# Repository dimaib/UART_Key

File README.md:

# Smart lock for city scooters
## Description
- This device allows you to block the scooter when charging, preventing premature removal from the rack
- The device also determines whether the scooter is rented or not, thereby blocking or giving it away
- Allows you to determine the speed of the scooter and dynamically change the color of the LED strip depending on the speed.
	>All data is intercepted from UART data line of the scooter.
## Tools and languages
- PCB and circuit diagram created by Altium Designer
- Firmware created in Keil uVision for ARM in C languages

## Main view PCB

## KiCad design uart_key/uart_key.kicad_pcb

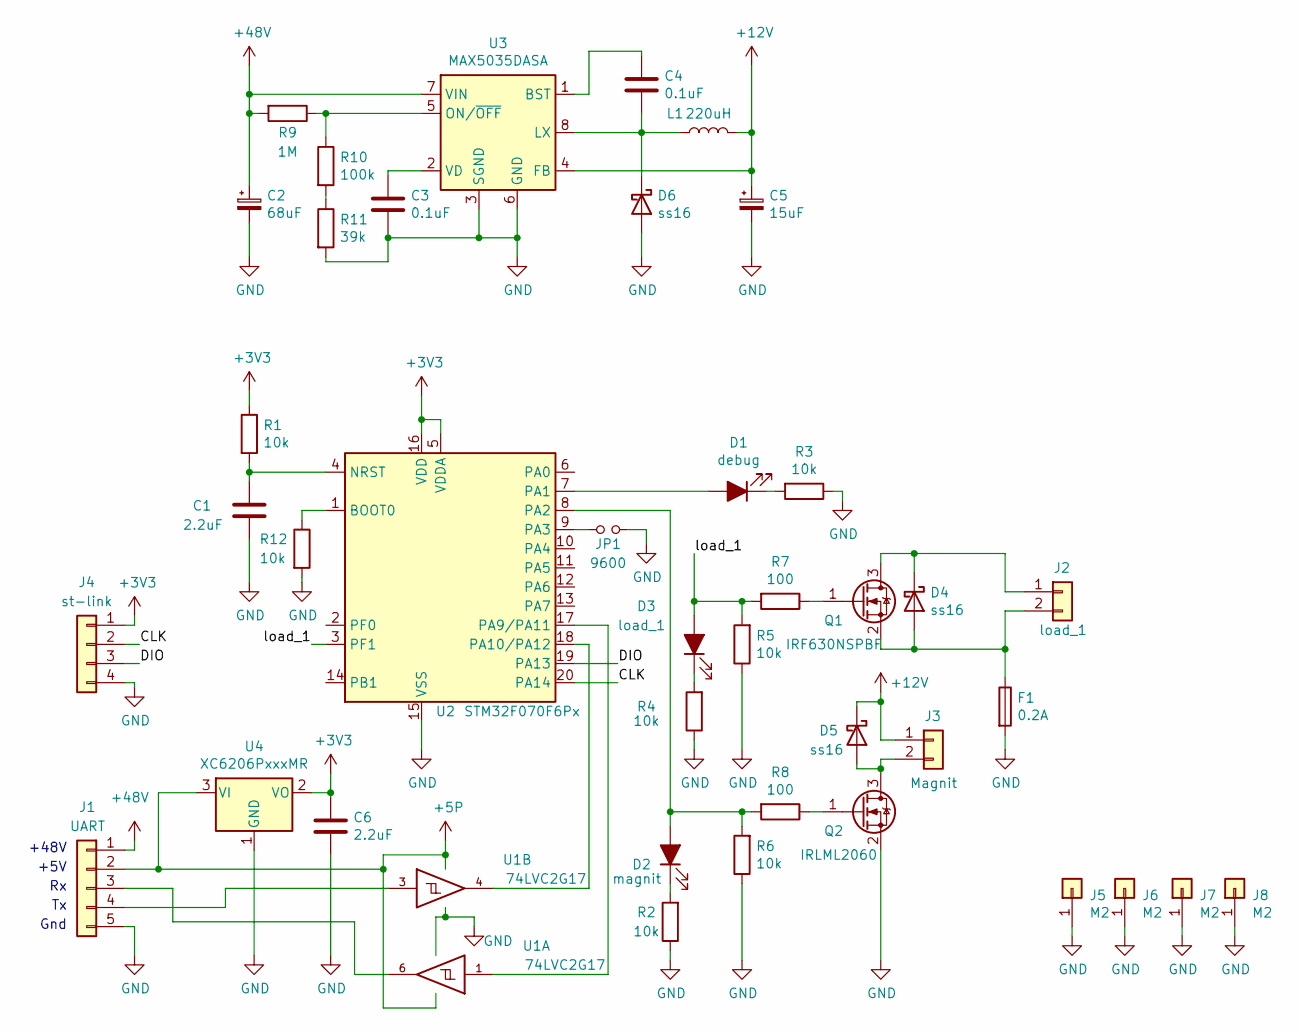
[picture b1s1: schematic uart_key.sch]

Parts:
C1, C6: 2.2uF; C_0603_1608Metric
C2: 68uF; CP_Elec_10x10.5
C3, C4: 0.1uF; C_0603_1608Metric
C5: 15uF; CP_EIA-3528-21_Kemet-B
D1: debug; LED_0603_1608Metric_Castellated
D2: magnit; LED_0603_1608Metric_Castellated
D3: load_1; LED_0603_1608Metric_Castellated
D4, D5, D6: ss16; D_SMA
F1: 0.2А; Fuse_1812_4532Metric
J1: UART; JST_XH_B5B-XH-A_1x05_P2.50mm_Vertical
J2: load_1; magnet_conn
J3: Magnit; ZH_Conn_02x01
J4: st-link; ZH_Conn_04x01
J5, J6, J7, J8: M2; MountingHole_2.2mm_M2_ISO7380_Pad_TopBottom
JP1: 9600; SolderJumper-2_P1.3mm_Open_TrianglePad1.0x1.5mm
L1: 220uH; L_10.4x10.4_H4.8
Q1: IRF630NSPBF; TO-263-2
Q2: IRLML2060; SOT-23
R1, R2, R3, R4, R5, R6, R12: 10k; R_0603_1608Metric
R7, R8: 100; R_0603_1608Metric
R9: 1M; R_0603_1608Metric
R10: 100k; R_0603_1608Metric
R11: 39k; R_0603_1608Metric
U1: 74LVC2G17; SOT-23-6
U2: STM32F070F6Px; TSSOP-20_4.4x6.5mm_P0.65mm
U3: MAX5035DASA; SOIC-8_3.9x4.9mm_P1.27mm
U4: XC6206PxxxMR; SOT-23

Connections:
+3V3: C6.1, J4.1, R1.1, U2.5 (VDDA), U2.16 (VDD), U4.2 (VO)
+5P: J1.2, U1.5 (VCC), U4.3 (VI)
+12V: C5.1, D5.1 (K), J3.1, L1.2, U3.4 (FB)
+48V: C2.1, J1.1, R9.2, U3.7 (VIN)
/CLK: J4.2, U2.20 (PA14)
/DIO: J4.3, U2.19 (PA13)
/load_1: D3.2 (A), R5.2, R7.2, U2.3 (PF1)
GND: C1.2, C2.2, C3.2, C5.2, C6.2, D6.2 (A), F1.2, J1.5, J4.4, J5.1, J6.1, J7.1, J8.1, JP1.2, Q2.2 (S), R2.1, R3.1, R4.1, R5.1, R6.1, R11.2, R12.2, U1.2 (GND), U2.15 (VSS), U3.3 (SGND), U3.6 (GND), U4.1 (GND)
unnamed: C1.1, R1.2, U2.4 (NRST)
unnamed: C3.1, U3.2 (VD)
unnamed: C4.1, U3.1 (BST)
unnamed: C4.2, D6.1 (K), L1.1, U3.8 (LX)
unnamed: D1.1 (K), R3.2
unnamed: D1.2 (A), U2.7 (PA1)
unnamed: D2.1 (K), R2.2
unnamed: D2.2 (A), R6.2, R8.2, U2.8 (PA2)
unnamed: D3.1 (K), R4.2
unnamed: D4.1 (K), J2.1, Q1.3 (D)
unnamed: D4.2 (A), F1.1, J2.2, Q1.2 (S)
unnamed: D5.2 (A), J3.2, Q2.3 (D)
unnamed: J1.3, U1.6
unnamed: J1.4, U1.3
unnamed: JP1.1, U2.9 (PA3)
unnamed: Q1.1 (G), R7.1
unnamed: Q2.1 (G), R8.1
unnamed: R9.1, R10.1, U3.5 (ON/~OFF~)
unnamed: R10.2, R11.1
unnamed: R12.1, U2.1 (BOOT0)
unnamed: U1.1, U2.17 (PA9/PA11)
unnamed: U1.4, U2.18 (PA10/PA12)

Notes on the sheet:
+5V
Gnd
+48V

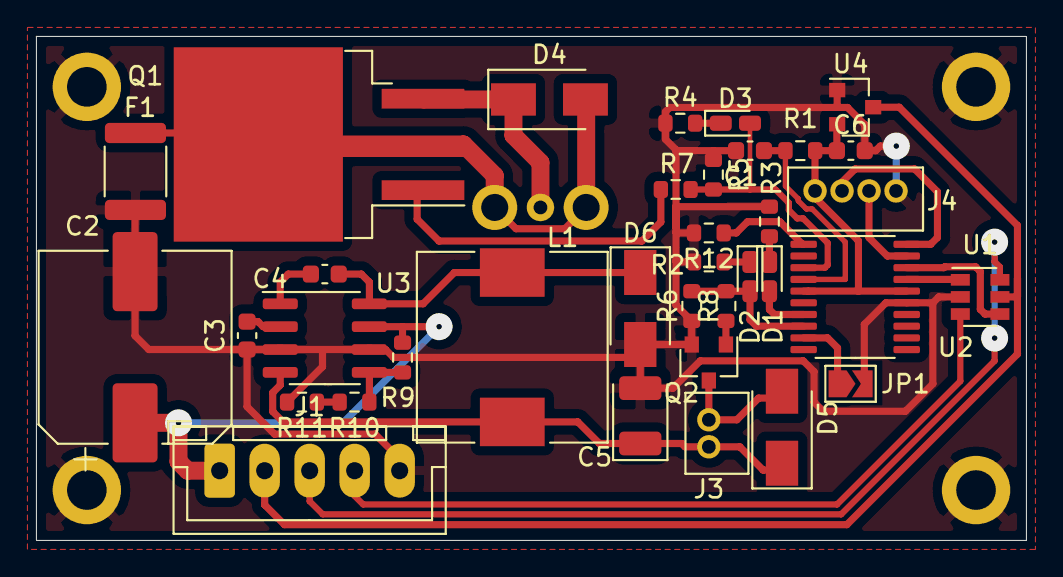
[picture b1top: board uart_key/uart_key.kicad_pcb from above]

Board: 2 copper layers, 55.0 x 28.0 mm, 41 parts (0 on the bottom side), 30 nets.

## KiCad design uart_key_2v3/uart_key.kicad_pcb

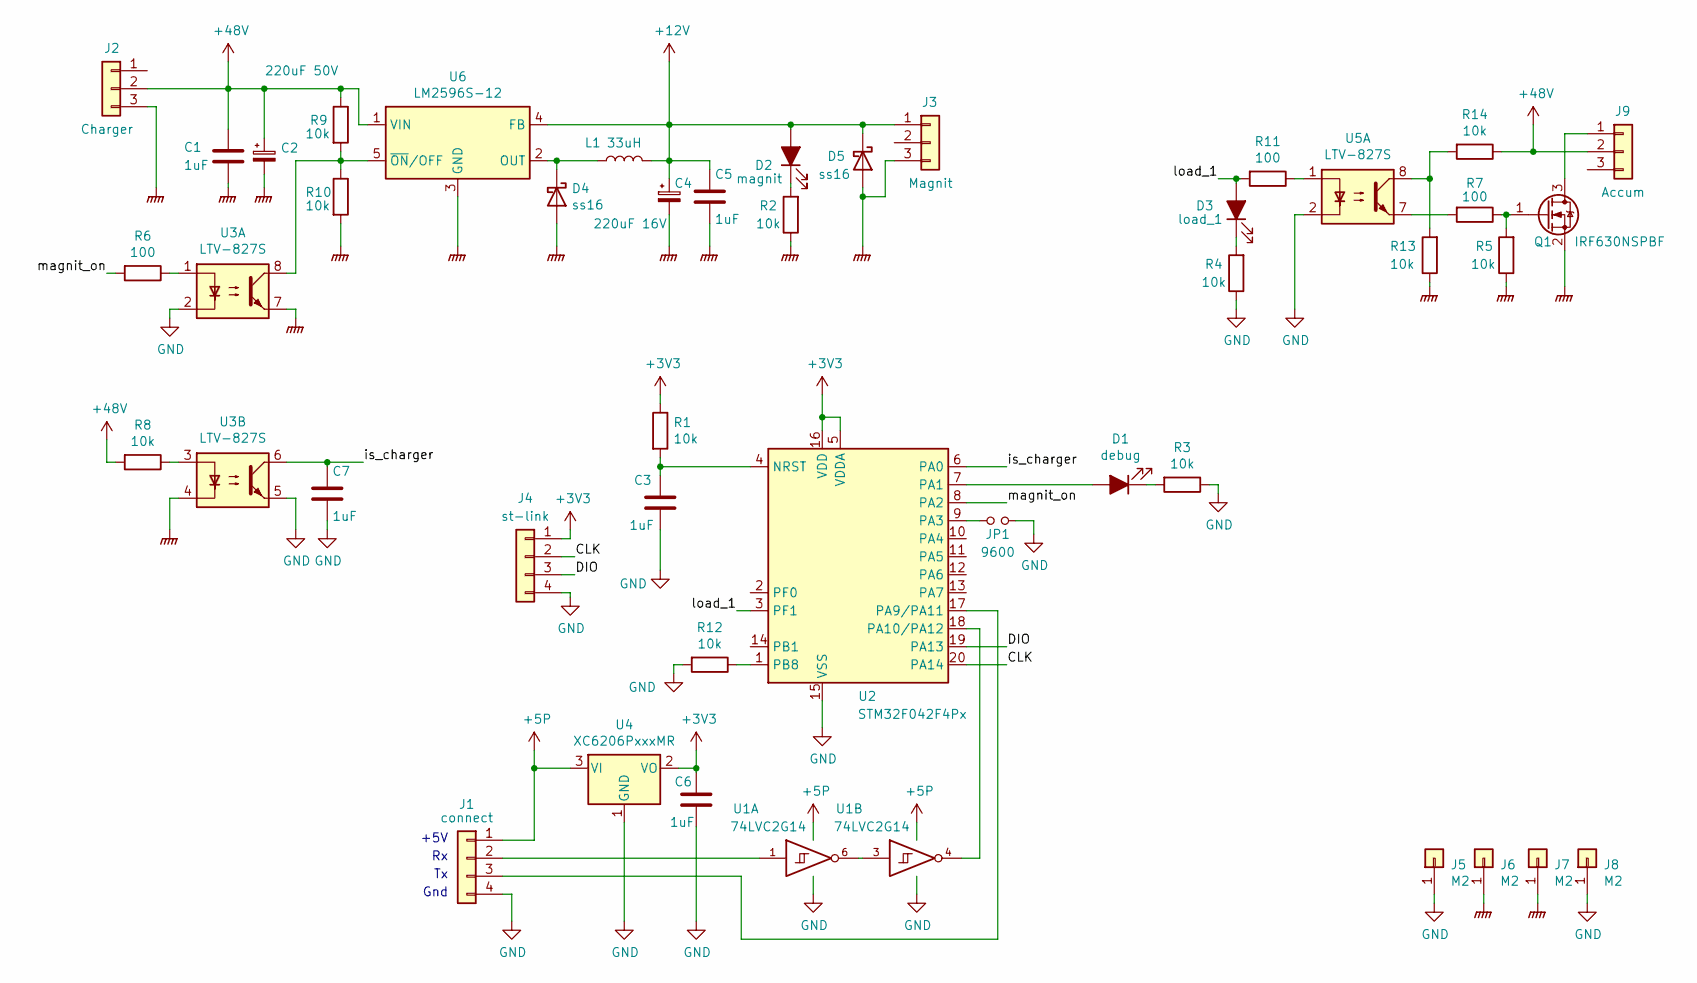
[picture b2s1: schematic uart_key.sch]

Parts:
C1, C3, C5, C6, C7: 1uF; C_0603_1608Metric
C2: 220uF 50V; CP_Elec_10x10.5
C4: 220uF 16V; CP_Elec_6.3x7.7
D1: debug; LED_0603_1608Metric_Castellated
D2: magnit; LED_0603_1608Metric_Castellated
D3: load_1; LED_0603_1608Metric_Castellated
D4, D5: ss16; D_SMA
J1: connect; JST_XH_B4B-XH-A_1x04_P2.50mm_Vertical
J2: Charger; JST_XH_B3B-XH-A_1x03_P2.50mm_Vertical
J3: Magnit; JST_XH_B3B-XH-A_1x03_P2.50mm_Vertical
J4: st-link; ZH_Conn_04x01
J5, J6, J7, J8: M2; MountingHole_2.2mm_M2_Pad_Via
J9: Accum; JST_XH_B3B-XH-A_1x03_P2.50mm_Vertical
JP1: 9600; PinHeader_1x02_P2.54mm_Vertical
L1: 33uH; SDR_1006
Q1: IRF630NSPBF; TO-263-2
R1, R2, R3, R4, R5, R8, R9, R10, R12, R13, R14: 10k; R_0603_1608Metric
R6, R7, R11: 100; R_0603_1608Metric
U1: 74LVC2G14; SOT-23-6
U2: STM32F042F4Px; TSSOP-20_4.4x6.5mm_P0.65mm
U3, U5: LTV-827S; SMDIP-8_W9.53mm
U4: XC6206PxxxMR; SOT-23
U6: LM2596S-12; TO-263-5_TabPin3

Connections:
+3V3: C6.1, J4.1, R1.1, U2.5 (VDDA), U2.16 (VDD), U4.2 (VO)
+5P: J1.1, U1.5 (VCC), U4.3 (VI)
+12V: C4.1, C5.1, D2.2 (A), D5.1 (K), J3.1, L1.2, U6.4 (FB)
+48V: C1.1, C2.1, J2.2, J9.2, R8.2, R9.1, R14.1, U6.1 (VIN)
/CLK: J4.2, U2.20 (PA14)
/DIO: J4.3, U2.19 (PA13)
/is_charger: C7.1, U2.6 (PA0), U3.6
/load_1: D3.2 (A), R11.2, U2.3 (PF1)
/magnit_on: R6.2, U2.8 (PA2)
GND: C3.2, C6.2, C7.2, J1.4, J4.4, J5.1, J8.1, JP1.2, R3.1, R4.1, R12.2, U1.2 (GND), U2.15 (VSS), U3.2, U3.5, U4.1 (GND), U5.2
GNDPWR: C1.2, C2.2, C4.2, C5.2, D4.2 (A), D5.2 (A), J2.3, J3.3, J6.1, J7.1, Q1.2 (S), R2.1, R5.1, R10.2, R13.1, U3.4, U3.7, U6.3 (GND)
unnamed: C3.1, R1.2, U2.4 (NRST)
unnamed: D1.1 (K), R3.2
unnamed: D1.2 (A), U2.7 (PA1)
unnamed: D2.1 (K), R2.2
unnamed: D3.1 (K), R4.2
unnamed: D4.1 (K), L1.1, U6.2 (OUT)
unnamed: J1.2, U1.1
unnamed: J1.3, U2.17 (PA9/PA11)
unnamed: J9.1, Q1.3 (D)
unnamed: JP1.1, U2.9 (PA3)
unnamed: Q1.1 (G), R5.2, R7.1
unnamed: R6.1, U3.1
unnamed: R7.2, U5.7
unnamed: R8.1, U3.3
unnamed: R9.2, R10.1, U3.8, U6.5 (~ON~/OFF)
unnamed: R11.1, U5.1
unnamed: R12.1, U2.1 (PB8)
unnamed: R13.2, R14.2, U5.8
unnamed: U1.3, U1.6
unnamed: U1.4, U2.18 (PA10/PA12)

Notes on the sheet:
+5V
Gnd

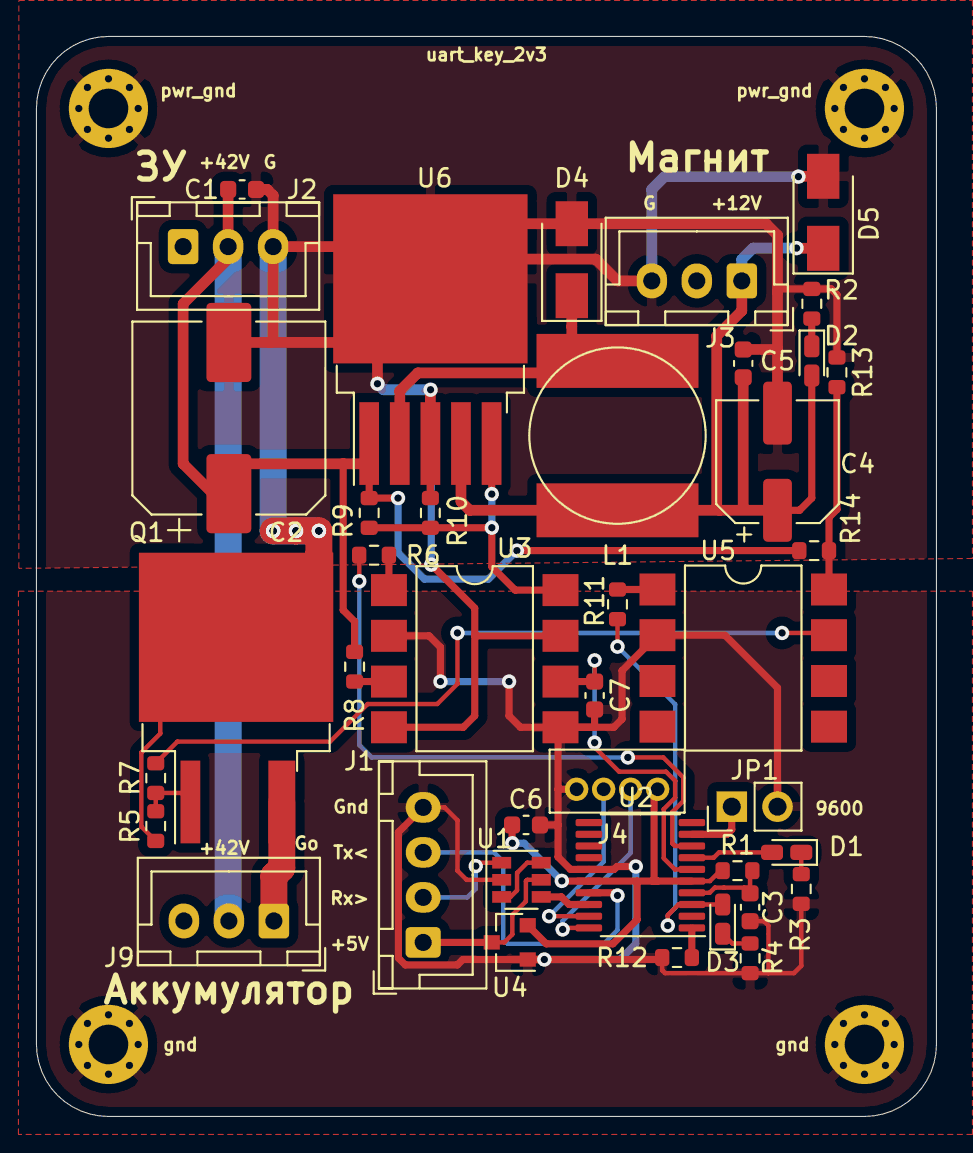
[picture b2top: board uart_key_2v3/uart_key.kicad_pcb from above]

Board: 2 copper layers, 50.0 x 60.0 mm, 44 parts (0 on the bottom side), 31 nets.

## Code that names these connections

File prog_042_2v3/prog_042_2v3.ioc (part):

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Mcu.Name=STM32F042F4Px
Mcu.Package=TSSOP20
Mcu.UserName=STM32F042F4Px
PA0.GPIOParameters=GPIO_PuPd,GPIO_Label
PA0.GPIO_Label=is_charger
PA0.GPIO_PuPd=GPIO_PULLUP
PA0.Signal=GPIO_Input
PA1.GPIOParameters=GPIO_Label
PA1.GPIO_Label=debug_led
PA1.Signal=GPIO_Output
PA10.Mode=Asynchronous
PA10.Signal=USART1_RX
PA13.Mode=Serial_Wire
PA13.Signal=SYS_SWDIO
PA14.Mode=Serial_Wire
PA14.Signal=SYS_SWCLK
PA2.GPIOParameters=GPIO_Label
PA2.GPIO_Label=magnit_on
PA2.Signal=GPIO_Output
PA3.GPIOParameters=GPIO_PuPd,GPIO_Label
PA3.GPIO_Label=baudrate
PA3.GPIO_PuPd=GPIO_PULLUP
PA3.Signal=GPIO_Input
PA9.Mode=Asynchronous
PA9.Signal=USART1_TX
PF1-OSC_OUT.GPIOParameters=GPIO_Label
PF1-OSC_OUT.GPIO_Label=load1_on
PF1-OSC_OUT.Signal=GPIO_Output
RCC.SYSCLKFreq_VALUE=48000000
RCC.SYSCLKSource=RCC_SYSCLKSOURCE_HSI48
board=custom

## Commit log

2022-04-20 add readme and sreen
2022-04-20 edit readme
